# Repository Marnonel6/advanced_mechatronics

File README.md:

# Advanced Meachatronic projects with the [`PIC32MX170F256B`](https://www.microchip.com/en-us/product/PIC32MX170F256B) chip:

- [(hw2) Basic circuit for PIC32MX170F256B `Circuit design`](https://github.com/Marnonel6/advanced_mechatronics/tree/main/hw2)
- [(hw3) `UART` communication & live Python data plotting](https://github.com/Marnonel6/advanced_mechatronics/tree/main/hw3)
- [(hw4) `PCB design` - KiCad](https://github.com/Marnonel6/advanced_mechatronics/tree/main/hw4)
- [(hw5) `SPI` communication with a DAC](https://github.com/Marnonel6/advanced_mechatronics/tree/main/hw5)
- [(hw6) `I2C` communication with a 8-Bit I2C I/O Expander ](https://github.com/Marnonel6/advanced_mechatronics/tree/main/hw6)
- [(hw7) `I2C` communication with a IMU - MPU6050](https://github.com/Marnonel6/advanced_mechatronics/tree/main/hw7)
- [(hw8) `I2C` communication with an OLED display and an IMU MPU6050](https://github.com/Marnonel6/advanced_mechatronics/tree/main/hw8)
- [(hw9) `Digital signal processing` on heartbeat data - Low and High-pass filters](https://github.com/Marnonel6/advanced_mechatronics/tree/main/hw9)
- [(hw10) `Neopixel`](https://github.com/Marnonel6/advanced_mechatronics/tree/main/hw10)
- [(hw11) `RPi` Pico W](https://github.com/Marnonel6/advanced_mechatronics/tree/main/hw11)
- [(hw12) DiffDrive `CAD` (OnShape)](https://github.com/Marnonel6/advanced_mechatronics/tree/main/hw12)
- [(hw14) DC `Motor control`](https://github.com/Marnonel6/advanced_mechatronics/tree/main/hw14)
- [(hw15) Line detection `CV` - RPi Pico](https://github.com/Marnonel6/advanced_mechatronics/tree/main/hw15)
- [(hw16) Line Follower - `Embedded systems`, CV, `PIC32`](https://github.com/Marnonel6/advanced_mechatronics/tree/main/hw16)

The following software is necessary:
- [MPLAB X IDE (v6.05)](https://www.microchip.com/en-us/tools-resources/develop/mplab-x-ide)
- [MPLAB XC32 C-Compiler (v4.21)](https://www.microchip.com/en-us/tools-resources/develop/mplab-xc-compilers)
- [Onshape](https://www.onshape.com/en/)
- [KiCad](https://www.kicad.org/)
- [Python3](https://www.python.org/downloads/)

The PIC32 was preprogrammed with a bootloader (from ME333). We will use a program called nu32utility to send the compiled code to the PIC32 using a virtual serial port. To compile nu32utility you will need gcc. gcc is already on OSX and linux, and can be installed on Windows with mingw.

# [Final Project](https://github.com/Marnonel6/advanced_mechatronics/tree/main/hw16)
https://github.com/Marnonel6/advanced_mechatronics/assets/60977336/0a9354a2-5b61-4926-b785-c4b6b43be233

# Circuit schematic and photo

# KiCAD PCB:

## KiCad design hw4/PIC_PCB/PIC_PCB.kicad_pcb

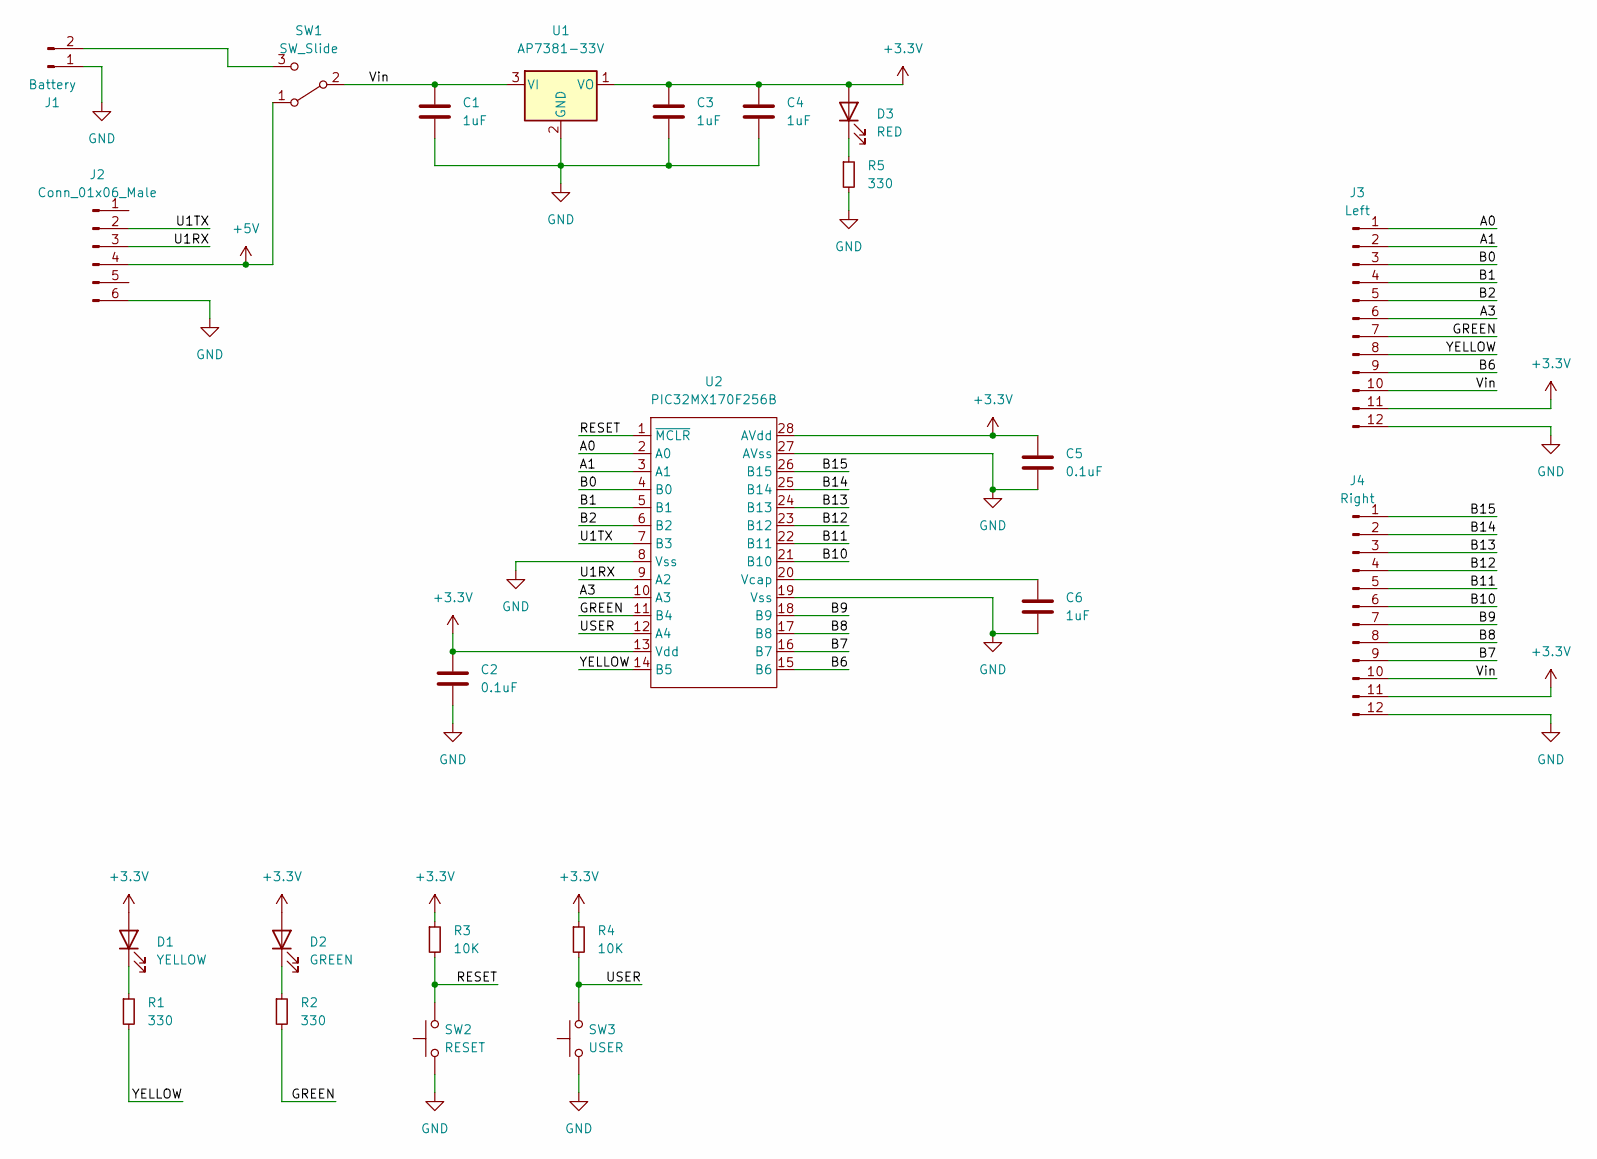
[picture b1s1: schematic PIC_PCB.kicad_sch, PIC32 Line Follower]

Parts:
C1, C3, C4, C6: 1uF; C_Disc_D3.4mm_W2.1mm_P2.50mm
C2, C5: 0.1uF; C_Disc_D3.8mm_W2.6mm_P2.50mm
D1: YELLOW; LED_D3.0mm
D2: GREEN; LED_D3.0mm
D3: RED; LED_D3.0mm
J1: Battery; PinSocket_1x02_P2.54mm_Vertical
J2: Conn_01x06_Male; PinSocket_1x06_P2.54mm_Vertical
J3: Left; PinSocket_1x12_P2.54mm_Vertical
J4: Right; PinSocket_1x12_P2.54mm_Vertical
R1, R2, R5: 330; R_Axial_DIN0207_L6.3mm_D2.5mm_P7.62mm_Horizontal
R3, R4: 10K; R_Axial_DIN0207_L6.3mm_D2.5mm_P7.62mm_Horizontal
SW1: SW_Slide; Slide_Switch
SW2: RESET; PinSocket_1x03_P2.54mm_Vertical
SW3: USER; PinSocket_1x03_P2.54mm_Vertical
U1: AP7381-33V; TO-92L_Inline
U2: PIC32MX170F256B; DIP-28_W7.62mm_Socket

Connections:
+3V3: C2.1, C3.1, C4.1, C5.1, D1.2 (A), D2.2 (A), D3.2 (A), J3.11, J4.11, R3.1, R4.1, U1.1 (VO), U2.13 (Vdd), U2.28 (AVdd)
+5V: J2.4, SW1.1 (A)
/A0: J3.1, U2.2 (A0)
/A1: J3.2, U2.3 (A1)
/A3: J3.6, U2.10 (A3)
/B0: J3.3, U2.4 (B0)
/B1: J3.4, U2.5 (B1)
/B2: J3.5, U2.6 (B2)
/B6: J3.9, U2.15 (B6)
/B7: J4.9, U2.16 (B7)
/B8: J4.8, U2.17 (B8)
/B9: J4.7, U2.18 (B9)
/B10: J4.6, U2.21 (B10)
/B11: J4.5, U2.22 (B11)
/B12: J4.4, U2.23 (B12)
/B13: J4.3, U2.24 (B13)
/B14: J4.2, U2.25 (B14)
/B15: J4.1, U2.26 (B15)
/GREEN: J3.7, R2.2, U2.11 (B4)
/RESET: R3.2, SW2.2, U2.1 (~MCLR)
/U1RX: J2.3, U2.9 (A2)
/U1TX: J2.2, U2.7 (B3)
/USER: R4.2, SW3.2, U2.12 (A4)
/Vin: C1.1, J3.10, J4.10, SW1.2 (B), U1.3 (VI)
/YELLOW: J3.8, R1.2, U2.14 (B5)
GND: C1.2, C2.2, C3.2, C4.2, C5.2, C6.2, J1.1, J2.6, J3.12, J4.12, R5.2, SW2.1, SW3.1, U1.2 (GND), U2.8 (Vss), U2.19 (Vss), U2.27 (AVss)
unnamed: C6.1, U2.20 (Vcap)
unnamed: D1.1 (K), R1.1
unnamed: D2.1 (K), R2.1
unnamed: D3.1 (K), R5.1
unnamed: J1.2, SW1.3 (C)

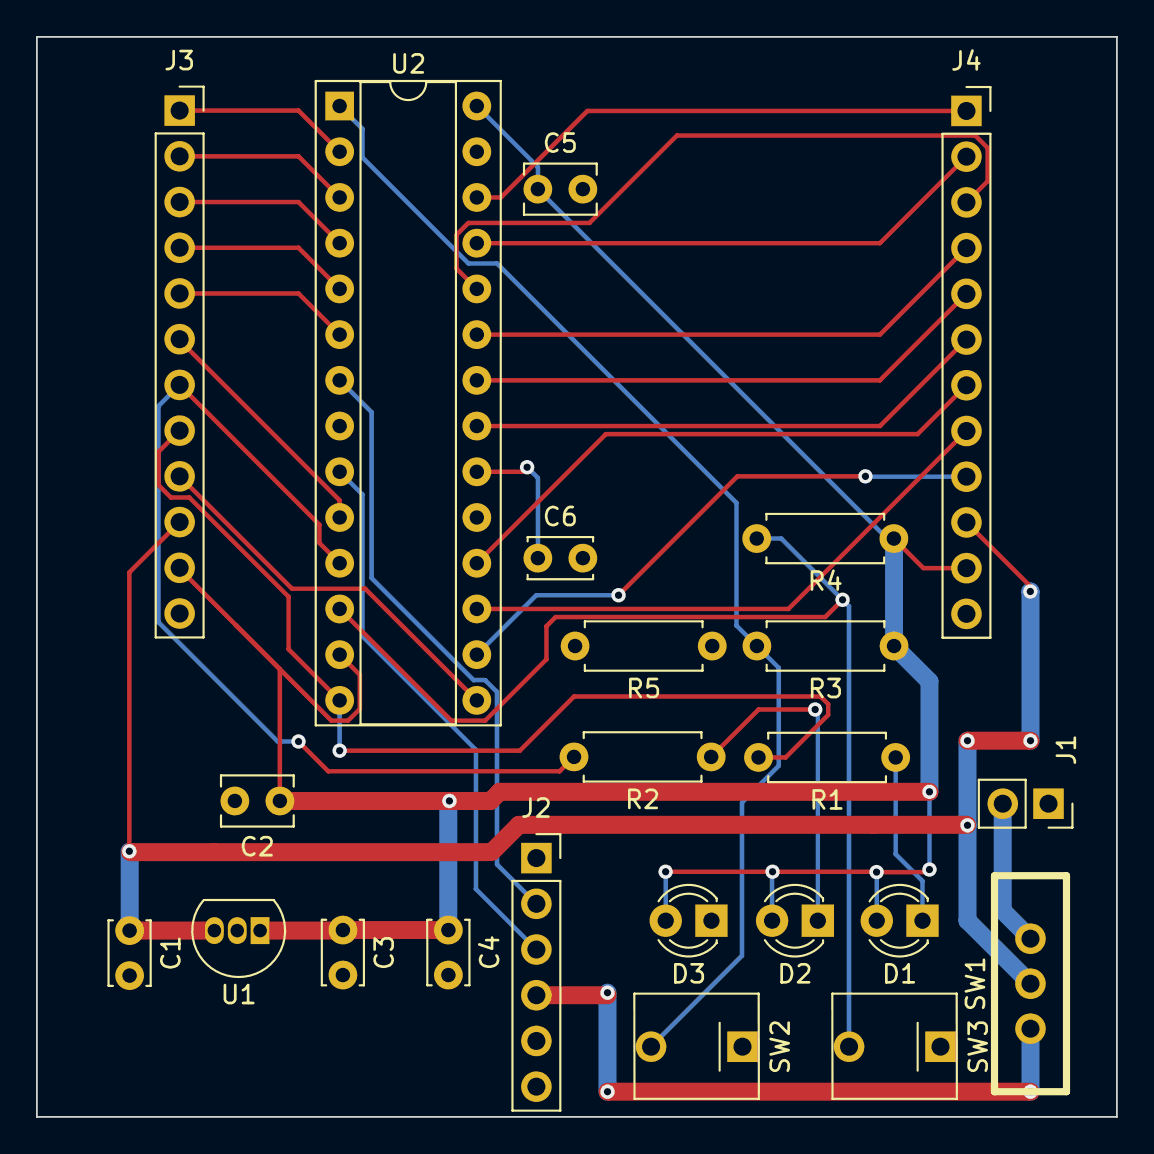
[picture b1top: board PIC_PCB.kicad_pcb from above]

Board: 2 copper layers, 60.0 x 60.0 mm, 23 parts (0 on the bottom side), 31 nets.

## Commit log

2023-04-04 Completed HW2
2023-04-04 Moved
2023-04-04 Added photos
2023-04-05 HW3 sine generator works
2023-04-05 Now works with button press now
2023-04-05 Update plotter for 500 points
2023-04-15 Started HW5 SPI DAC and improved KiCAD PCB
2023-04-16 1Hz Triangle wave works
2023-04-16 SPI setup works
2023-04-16 Triangle works
2023-04-16 Both triangle 1Hz and sine 2Hz works
2023-04-16 Done with SPI singals and HW5
2023-04-27 Added HeartBeat function to detect if code is stuck
2023-04-28 I2C works with GP7/LED being turned on when GP0/Button is pressed
2023-04-28 Generic I2C functions works!
2023-04-28 Moved files in HW6.x
2023-04-28 Updated location of source files
2023-04-28 Done with MPU6050 low level data read and plot
2023-04-29 String and char write works
2023-04-29 Screen scroll works and fps
2023-04-29 Done with OLED
2023-05-06 DOne with digital signal processing
2023-05-06 LED array works!
2023-05-15 Done with HW11
2023-05-26 Finished PCB
2023-06-04 Motor control works
2023-06-05 Both motors work
2023-06-05 Added new #define names for motor control
2023-06-05 Both motors work with new pins
2023-06-05 Cleaned code
2023-06-05 Updated wheel direction code
2023-06-07 Car follows the line
2023-06-07 Added camera line code
2023-06-08 Line follower works
2023-06-08 Done
2023-06-08 Added Pico code
2023-06-08 Servo control done
2023-06-08 Dervo control
